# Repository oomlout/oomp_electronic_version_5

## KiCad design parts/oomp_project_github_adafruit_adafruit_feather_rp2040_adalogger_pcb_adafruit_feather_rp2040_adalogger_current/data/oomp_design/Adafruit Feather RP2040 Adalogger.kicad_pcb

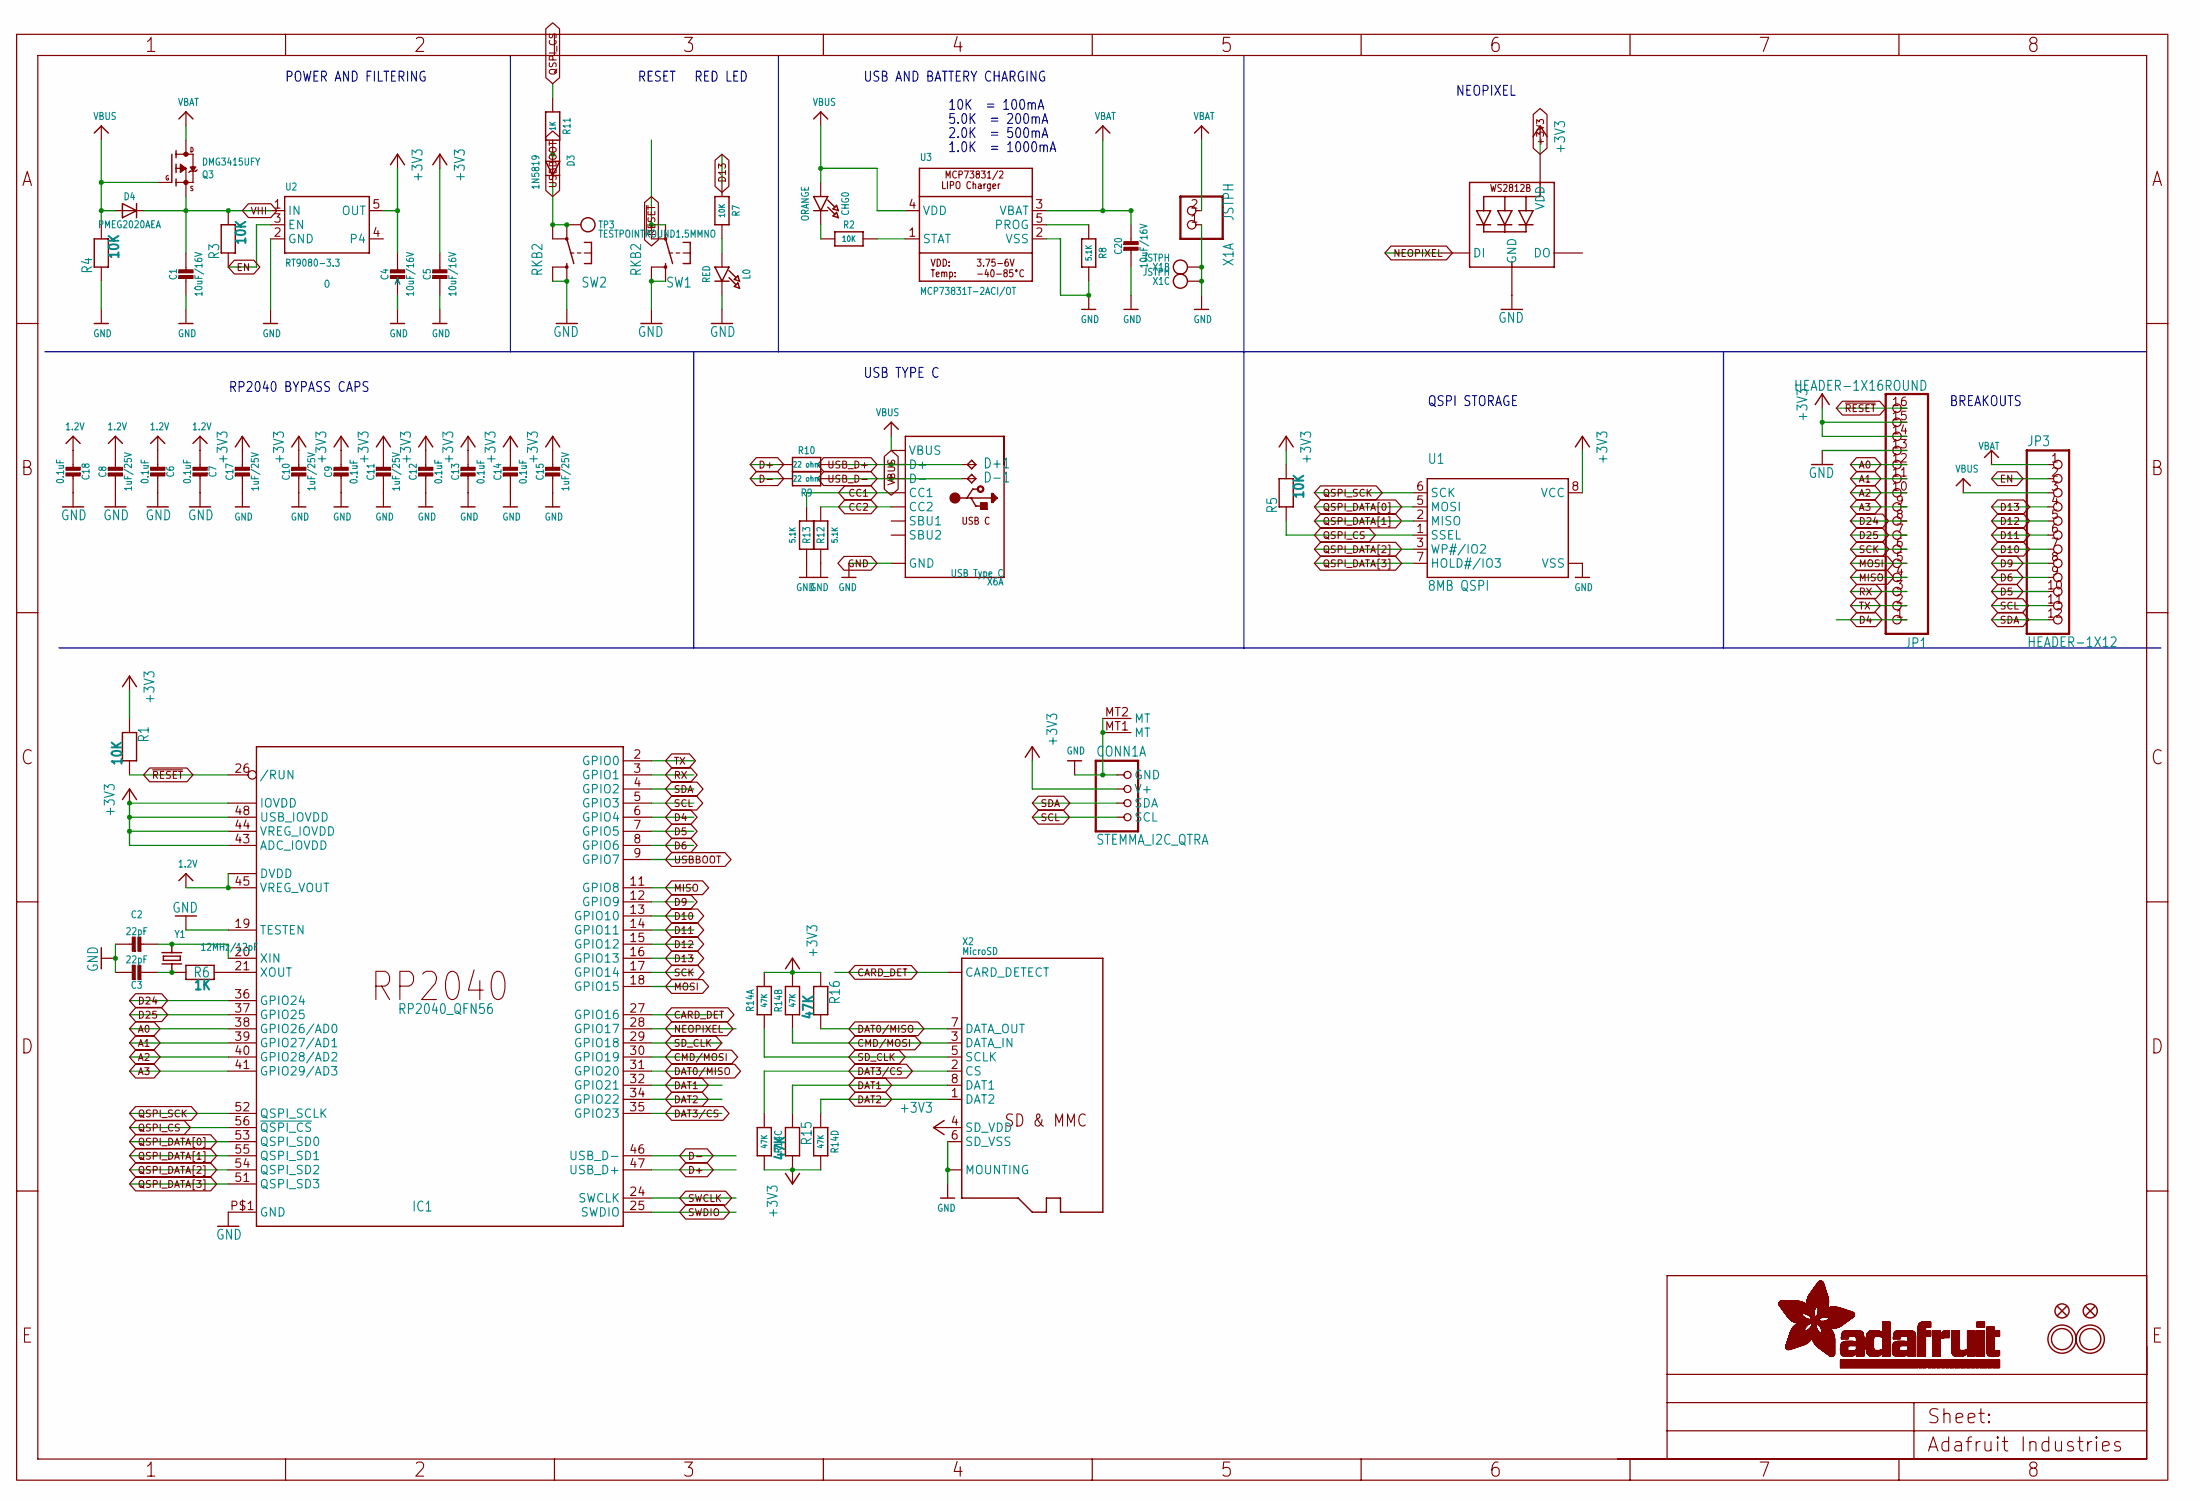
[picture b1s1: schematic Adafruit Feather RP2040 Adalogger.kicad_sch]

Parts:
C1, C4, C5, C20: 10uF/16V; 0805-NO
C2, C3: 22pF; _0402NO
C6, C7, C9, C12, C13, C14, C18: 0.1uF; _0402NO
C8, C10, C11, C15, C17: 1uF/25V; _0402NO
CHG0: ORANGE; CHIPLED_0603_NOOUTLINE
CONN1: STEMMA_I2C_QTRA; JST_SH4_RA; LCSC C145961
D3: 1N5819; SOD-323_MINI
D4: PMEG2020AEA; SOD-323F
D+1: TPB1,27; B1,27
D-1: TPB1,27; B1,27
IC1: RP2040_QFN56; QFN56_7MM_REDUCEDEPAD; LCSC C2040
JP1: HEADER-1X16ROUND; 1X16_ROUND
JP3: HEADER-1X12; 1X12_ROUND
L0: RED; CHIPLED_0603_NOOUTLINE
LED1: WS2812B_SK6805_1515; SK6805_1515; LCSC C2890035
Q3: DMG3415UFY; DFN2015-3
R1, R2, R3, R4, R5, R7: 10K; _0402NO
R6, R11: 1K; _0402NO
R8, R12, R13: 5.1K; _0402NO
R9, R10: 22 ohm; _0402NO
R14: 47K; RESPACK_4X0603
R15, R16: 47K; _0402NO
SW1, SW2: RKB2; BTN_RKB2_4.6X2.8
TP3: TESTPOINTROUND1.5MMNO; TESTPOINT_ROUND_1.5MM_NO
U1: 8MB QSPI; USON8_4X4
U2: RT9080-3.3; SOT23-5; JLC_ROTATION 0
U3: MCP73831T-2ACI/OT; SOT23-5; JLC_ROTATION 0
U$31, U$32: MOUNTINGHOLE2.5; MOUNTINGHOLE_2.5_PLATED
U$34, U$35: FIDUCIAL_1MM
X1: JSTPH; JSTPH2_BATT; LCSC C47647
X2: MicroSD; MICROSD; JLC_ROTATION 90
X6: USB Type C; USB_C_CUSB31-CFM2AX-01-X; LCSC C165948
Y1: 12MHz/12pF; CRYSTAL_2.5X2

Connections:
1.2V: C6.2, C7.2, C8.1, C18.2, IC1.23 (DVDD), IC1.45 (VREG_VOUT), IC1.50 (DVDD)
+3V3: C4.1, C5.1, C9.1, C10.1, C11.1, C12.1, C13.1, C14.1, C15.1, C17.1, CONN1.2 (V+), IC1.1 (IOVDD), IC1.10 (IOVDD), IC1.22 (IOVDD), IC1.33 (IOVDD), IC1.42 (IOVDD), IC1.43 (ADC_IOVDD), IC1.44 (VREG_IOVDD), IC1.48 (USB_IOVDD), IC1.49 (IOVDD), JP1.14, JP1.15, LED1.2 (VDD), R1.1, R5.2, R14.5 (2), R14.6 (2), R14.7 (2), R14.8 (2), R15.2, R16.1, U1.8 (VCC), U2.5 (OUT), X2.4 (SD_VDD)
A0: IC1.38 (GPIO26/AD0), JP1.12
A1: IC1.39 (GPIO27/AD1), JP1.11
A2: IC1.40 (GPIO28/AD2), JP1.10
A3: IC1.41 (GPIO29/AD3), JP1.9
CARD_DET: IC1.27 (GPIO16), X2.CD1 (CARD_DETECT), X2.CD2 (CARD_DETECT)
CC1: R13.2, X6.A5 (CC1)
CC2: R12.2, X6.B5 (CC2)
CMD/MOSI: IC1.30 (GPIO19), R14.2 (1), X2.3 (DATA_IN)
D4: IC1.6 (GPIO4), JP1.1
D5: IC1.7 (GPIO5), JP3.10
D6: IC1.8 (GPIO6), JP3.9
D9: IC1.12 (GPIO9), JP3.8
D10: IC1.13 (GPIO10), JP3.7
D11: IC1.14 (GPIO11), JP3.6
D12: IC1.15 (GPIO12), JP3.5
D13: IC1.16 (GPIO13), JP3.4, R7.1
D24: IC1.36 (GPIO24), JP1.8
D25: IC1.37 (GPIO25), JP1.7
D+: IC1.47 (USB_D+), R10.2
D-: IC1.46 (USB_D-), R9.2
DAT0/MISO: IC1.31 (GPIO20), R16.2, X2.7 (DATA_OUT)
DAT1: IC1.32 (GPIO21), R15.1, X2.8 (DAT1)
DAT2: IC1.34 (GPIO22), R14.4 (1), X2.1 (DAT2)
DAT3/CS: IC1.35 (GPIO23), R14.3 (1), X2.2 (CS)
EN: JP3.2, R3.1, U2.3 (EN)
GND: C1.2, C2.1, C3.1, C4.2, C5.2, C6.1, C7.1, C8.2, C9.2, C10.2, C11.2, C12.2, C13.2, C14.2, C15.2, C17.2, C18.1, C20.2, CONN1.1 (GND), CONN1.MT1 (MT), CONN1.MT2 (MT), IC1.19 (TESTEN), IC1.P$1 (GND), JP1.13, L0.C, LED1.4 (GND), R4.1, R8.2, R12.1, R13.1, SW1.B (S), SW1.B' (S1), SW2.B (S), SW2.B' (S1), U1.4 (VSS), U1.PAD (VSS), U2.2 (GND), U3.2 (VSS), X1.1, X1.NC1, X1.NC2, X2.6 (SD_VSS), X2.MT1 (MOUNTING), X2.MT2 (MOUNTING), X6.A1B12 (GND), X6.B1A12 (GND)
MISO: IC1.11 (GPIO8), JP1.4
MOSI: IC1.18 (GPIO15), JP1.5
unnamed: CHG0.C, R2.1
unnamed: L0.A, R7.2
unnamed: R2.2, U3.1 (STAT)
unnamed: R8.1, U3.5 (PROG)
unnamed: C2.2, IC1.20 (XIN), Y1.3 (2)
unnamed: C3.2, R6.1, Y1.1
unnamed: IC1.21 (XOUT), R6.2
unnamed: D3.A, R11.2
NEOPIXEL: IC1.28 (GPIO17), LED1.1 (DI)
QSPI_CS: IC1.56 (~QSPI_CS), R5.1, R11.1, U1.1 (SSEL)
QSPI_DATA[0]: IC1.53 (QSPI_SD0), U1.5 (MOSI)
QSPI_DATA[1]: IC1.55 (QSPI_SD1), U1.2 (MISO)
QSPI_DATA[2]: IC1.54 (QSPI_SD2), U1.3 (WP#/IO2)
QSPI_DATA[3]: IC1.51 (QSPI_SD3), U1.7 (HOLD#/IO3)
QSPI_SCK: IC1.52 (QSPI_SCLK), U1.6 (SCK)
RX: IC1.3 (GPIO1), JP1.3
SCK: IC1.17 (GPIO14), JP1.6
SCL: CONN1.4 (SCL), IC1.5 (GPIO3), JP3.11
SDA: CONN1.3 (SDA), IC1.4 (GPIO2), JP3.12
SD_CLK: IC1.29 (GPIO18), R14.1, X2.5 (SCLK)
SWCLK: IC1.24 (SWCLK)
SWDIO: IC1.25 (SWDIO)
TX: IC1.2 (GPIO0), JP1.2
USBBOOT: D3.C, IC1.9 (GPIO7), SW2.A, SW2.A' (P1), TP3.P$1
USB_D+: D+1.TP, R10.1, X6.A6 (D+), X6.B6 (D+)
USB_D-: D-1.TP, R9.1, X6.A7 (D-), X6.B7 (D-)
VBAT: C20.1, JP3.1, Q3.3 (D), U3.3 (VBAT), X1.2
VBUS: CHG0.A, D4.A, JP3.3, Q3.1 (G), R4.2, U3.4 (VDD), X6.A4B9 (VBUS), X6.B4A9 (VBUS)
VHI: C1.1, D4.C, Q3.2 (S), R3.2, U2.1 (IN)
~RESET: IC1.26 (/RUN), JP1.16, R1.2, SW1.A, SW1.A' (P1)

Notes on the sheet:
RP2040 BYPASS CAPS
POWER AND FILTERING
NEOPIXEL
QSPI STORAGE
USB AND BATTERY CHARGING
5.0K = 200mA
BREAKOUTS
RESET
10K = 100mA
RED LED
1.0K = 1000mA
2.0K = 500mA
USB TYPE C

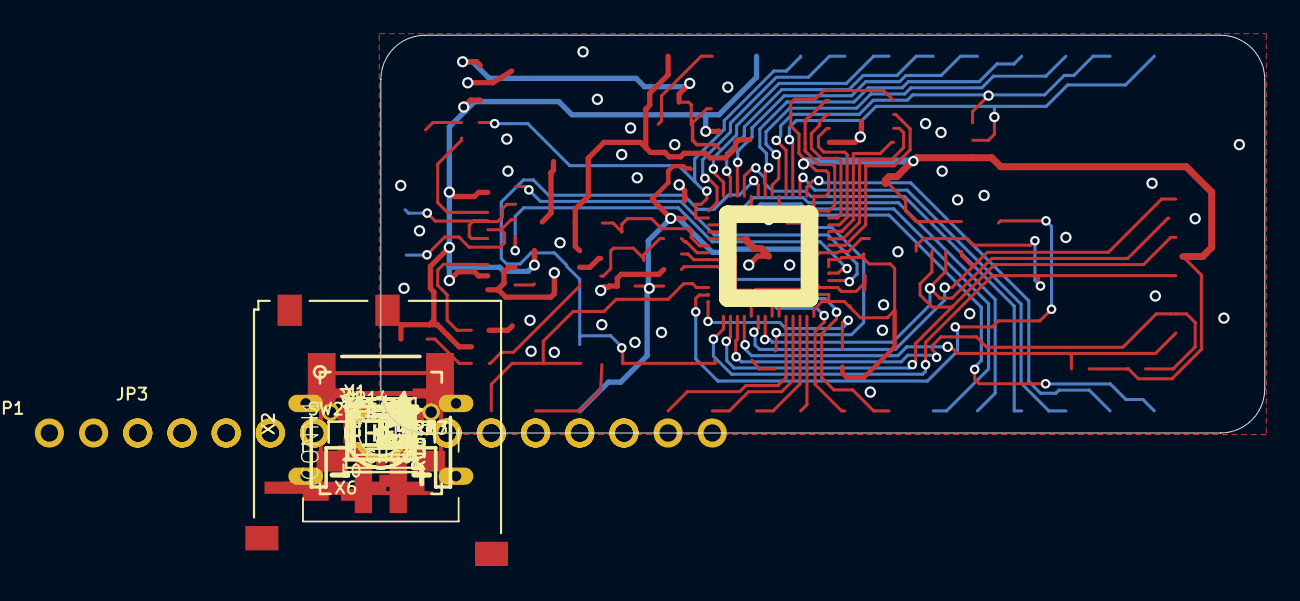
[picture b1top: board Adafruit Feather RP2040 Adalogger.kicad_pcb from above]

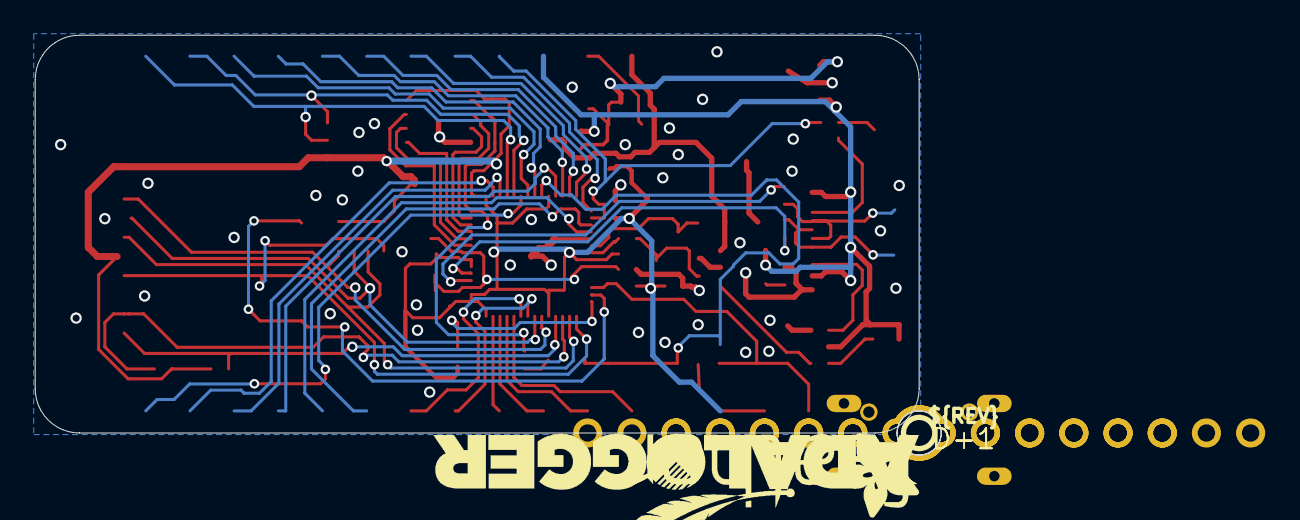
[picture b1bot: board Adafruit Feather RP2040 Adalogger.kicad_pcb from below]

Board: 2 copper layers, 50.8 x 22.9 mm, 130 parts (37 on the bottom side), 58 nets.

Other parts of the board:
PLABEL62: PLABEL62
PLABEL63: PLABEL63
PLABEL64: PLABEL64
PLABEL65: PLABEL65
PLABEL66: PLABEL66
PLABEL67: PLABEL67
PLABEL68: PLABEL68
PLABEL69: PLABEL69
PLABEL70: PLABEL70
PLABEL71: PLABEL71
PLABEL72: PLABEL72
PLABEL73: PLABEL73
PLABEL74: PLABEL74
PLABEL75: PLABEL75
PLABEL76: PLABEL76
PLABEL77: PLABEL77
PLABEL78: PLABEL78
PLABEL79: PLABEL79
PLABEL80: PLABEL80
PLABEL81: PLABEL81
PLABEL82: PLABEL82
PLABEL83: PLABEL83
PLABEL84: PLABEL84
PLABEL85: PLABEL85
PLABEL86: PLABEL86
PLABEL87: PLABEL87
PLABEL88: PLABEL88
PLABEL89: PLABEL89
PLABEL90: PLABEL90
PLABEL91: PLABEL91
PLABEL92: PLABEL92
PLABEL93: PLABEL93
PLABEL94: PLABEL94
PLABEL95: PLABEL95
PLABEL96: PLABEL96
PLABEL97: PLABEL97
PLABEL98: PLABEL98
PLABEL99: PLABEL99
PLABEL100: PLABEL100
PLABEL101: PLABEL101
PLABEL102: PLABEL102
PLABEL103: PLABEL103
PLABEL104: PLABEL104
PLABEL105: PLABEL105
PLABEL106: PLABEL106
PLABEL107: PLABEL107
PLABEL108: PLABEL108
PLABEL109: PLABEL109
PLABEL110: PLABEL110
PLABEL111: PLABEL111
PLABEL112: PLABEL112
PLABEL113: PLABEL113
PLABEL114: PLABEL114
PLABEL115: PLABEL115
PLABEL116: PLABEL116
PLABEL117: PLABEL117
PLABEL118: PLABEL118
PLABEL119: PLABEL119
PLABEL120: PLABEL120
PLABEL121: PLABEL121
PLABEL122: PLABEL122
PLABEL123: PLABEL123
PLABEL124: PLABEL124
U$13: PCBFEAT-REV-040
U$28: ADALOGGER_LOGO
U$43: ADAFRUIT_2.5MM
U$46: FEATHERLOGO_MED
U$47: ADAFRUIT_5MM
UNK_HOLE_0: dummyfp0
UNK_HOLE_1: dummyfp1

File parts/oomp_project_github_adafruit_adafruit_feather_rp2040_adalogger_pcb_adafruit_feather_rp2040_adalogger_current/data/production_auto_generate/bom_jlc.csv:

Comment,Designator,Footprint,LCSC Part #
,JP3,Adafruit Feather RP2040 Adalogger-import-fps:1X12_ROUND,C7501588
,JP1,Adafruit Feather RP2040 Adalogger-import-fps:1X16_ROUND,C7501270
,U$43,Adafruit Feather RP2040 Adalogger-import-fps:ADAFRUIT_2.5MM,
,U$47,Adafruit Feather RP2040 Adalogger-import-fps:ADAFRUIT_5MM,
,U$28,Adafruit Feather RP2040 Adalogger-import-fps:ADALOGGER_LOGO,
,U$46,Adafruit Feather RP2040 Adalogger-import-fps:FEATHERLOGO_MED,
,U$13,Adafruit Feather RP2040 Adalogger-import-fps:PCBFEAT-REV-040,
,PLABEL100,Adafruit Feather RP2040 Adalogger-import-fps:PLABEL100,
,PLABEL101,Adafruit Feather RP2040 Adalogger-import-fps:PLABEL101,
,PLABEL102,Adafruit Feather RP2040 Adalogger-import-fps:PLABEL102,
,PLABEL103,Adafruit Feather RP2040 Adalogger-import-fps:PLABEL103,
,PLABEL104,Adafruit Feather RP2040 Adalogger-import-fps:PLABEL104,
,PLABEL105,Adafruit Feather RP2040 Adalogger-import-fps:PLABEL105,
,PLABEL106,Adafruit Feather RP2040 Adalogger-import-fps:PLABEL106,
,PLABEL107,Adafruit Feather RP2040 Adalogger-import-fps:PLABEL107,
,PLABEL108,Adafruit Feather RP2040 Adalogger-import-fps:PLABEL108,
,PLABEL109,Adafruit Feather RP2040 Adalogger-import-fps:PLABEL109,
,PLABEL110,Adafruit Feather RP2040 Adalogger-import-fps:PLABEL110,
,PLABEL111,Adafruit Feather RP2040 Adalogger-import-fps:PLABEL111,
,PLABEL112,Adafruit Feather RP2040 Adalogger-import-fps:PLABEL112,
,PLABEL113,Adafruit Feather RP2040 Adalogger-import-fps:PLABEL113,
,PLABEL114,Adafruit Feather RP2040 Adalogger-import-fps:PLABEL114,
,PLABEL115,Adafruit Feather RP2040 Adalogger-import-fps:PLABEL115,
,PLABEL116,Adafruit Feather RP2040 Adalogger-import-fps:PLABEL116,
,PLABEL117,Adafruit Feather RP2040 Adalogger-import-fps:PLABEL117,
,PLABEL118,Adafruit Feather RP2040 Adalogger-import-fps:PLABEL118,
,PLABEL119,Adafruit Feather RP2040 Adalogger-import-fps:PLABEL119,
,PLABEL120,Adafruit Feather RP2040 Adalogger-import-fps:PLABEL120,
,PLABEL121,Adafruit Feather RP2040 Adalogger-import-fps:PLABEL121,
,PLABEL122,Adafruit Feather RP2040 Adalogger-import-fps:PLABEL122,
,PLABEL123,Adafruit Feather RP2040 Adalogger-import-fps:PLABEL123,
,PLABEL124,Adafruit Feather RP2040 Adalogger-import-fps:PLABEL124,
,PLABEL62,Adafruit Feather RP2040 Adalogger-import-fps:PLABEL62,
,PLABEL63,Adafruit Feather RP2040 Adalogger-import-fps:PLABEL63,
,PLABEL64,Adafruit Feather RP2040 Adalogger-import-fps:PLABEL64,
,PLABEL65,Adafruit Feather RP2040 Adalogger-import-fps:PLABEL65,
,PLABEL66,Adafruit Feather RP2040 Adalogger-import-fps:PLABEL66,
,PLABEL67,Adafruit Feather RP2040 Adalogger-import-fps:PLABEL67,
,PLABEL68,Adafruit Feather RP2040 Adalogger-import-fps:PLABEL68,
,PLABEL69,Adafruit Feather RP2040 Adalogger-import-fps:PLABEL69,
,PLABEL70,Adafruit Feather RP2040 Adalogger-import-fps:PLABEL70,
,PLABEL71,Adafruit Feather RP2040 Adalogger-import-fps:PLABEL71,
,PLABEL72,Adafruit Feather RP2040 Adalogger-import-fps:PLABEL72,
,PLABEL73,Adafruit Feather RP2040 Adalogger-import-fps:PLABEL73,
,PLABEL74,Adafruit Feather RP2040 Adalogger-import-fps:PLABEL74,
,PLABEL75,Adafruit Feather RP2040 Adalogger-import-fps:PLABEL75,
,PLABEL76,Adafruit Feather RP2040 Adalogger-import-fps:PLABEL76,
,PLABEL77,Adafruit Feather RP2040 Adalogger-import-fps:PLABEL77,
,PLABEL78,Adafruit Feather RP2040 Adalogger-import-fps:PLABEL78,
,PLABEL79,Adafruit Feather RP2040 Adalogger-import-fps:PLABEL79,
,PLABEL80,Adafruit Feather RP2040 Adalogger-import-fps:PLABEL80,
,PLABEL81,Adafruit Feather RP2040 Adalogger-import-fps:PLABEL81,
,PLABEL82,Adafruit Feather RP2040 Adalogger-import-fps:PLABEL82,
,PLABEL83,Adafruit Feather RP2040 Adalogger-import-fps:PLABEL83,
,PLABEL84,Adafruit Feather RP2040 Adalogger-import-fps:PLABEL84,
,PLABEL85,Adafruit Feather RP2040 Adalogger-import-fps:PLABEL85,
,PLABEL86,Adafruit Feather RP2040 Adalogger-import-fps:PLABEL86,
,PLABEL87,Adafruit Feather RP2040 Adalogger-import-fps:PLABEL87,
,PLABEL88,Adafruit Feather RP2040 Adalogger-import-fps:PLABEL88,
,PLABEL89,Adafruit Feather RP2040 Adalogger-import-fps:PLABEL89,
,PLABEL90,Adafruit Feather RP2040 Adalogger-import-fps:PLABEL90,
,PLABEL91,Adafruit Feather RP2040 Adalogger-import-fps:PLABEL91,
,PLABEL92,Adafruit Feather RP2040 Adalogger-import-fps:PLABEL92,
,PLABEL93,Adafruit Feather RP2040 Adalogger-import-fps:PLABEL93,
,PLABEL94,Adafruit Feather RP2040 Adalogger-import-fps:PLABEL94,
,PLABEL95,Adafruit Feather RP2040 Adalogger-import-fps:PLABEL95,
,PLABEL96,Adafruit Feather RP2040 Adalogger-import-fps:PLABEL96,
,PLABEL97,Adafruit Feather RP2040 Adalogger-import-fps:PLABEL97,
,PLABEL98,Adafruit Feather RP2040 Adalogger-import-fps:PLABEL98,
,PLABEL99,Adafruit Feather RP2040 Adalogger-import-fps:PLABEL99,
,TP3,Adafruit Feather RP2040 Adalogger-import-fps:TESTPOINT_ROUND_1.5MM_NO,
0.1uF,"C6,C7,C9,C12,C13,C14,C18",Adafruit Feather RP2040 Adalogger-import-fps:_0402NO,C60474
10K,"R1,R2,R3,R4,R5,R7",Adafruit Feather RP2040 Adalogger-import-fps:_0402NO,C2906861
10uF/16V,"C1,C4,C5,C20",Adafruit Feather RP2040 Adalogger-import-fps:0805-NO,
12MHz/12pF,Y1,Adafruit Feather RP2040 Adalogger-import-fps:CRYSTAL_2.5X2,
1K,"R6,R11",Adafruit Feather RP2040 Adalogger-import-fps:_0402NO,C2906864
1N5819,D3,Adafruit Feather RP2040 Adalogger-import-fps:SOD-323_MINI,
1uF/25V,"C8,C10,C11,C15,C17",Adafruit Feather RP2040 Adalogger-import-fps:_0402NO,C2887021
22 ohm,"R9,R10",Adafruit Feather RP2040 Adalogger-import-fps:_0402NO,C114765
22pF,"C2,C3",Adafruit Feather RP2040 Adalogger-import-fps:_0402NO,C106203
47K,"R15,R16",Adafruit Feather RP2040 Adalogger-import-fps:_0402NO,C25792
47K,R14,Adafruit Feather RP2040 Adalogger-import-fps:RESPACK_4X0603,C2907042
5.1K,"R8,R12,R13",Adafruit Feather RP2040 Adalogger-import-fps:_0402NO,C25905
8MB QSPI,U1,Adafruit Feather RP2040 Adalogger-import-fps:USON8_4X4,
DMG3415UFY,Q3,Adafruit Feather RP2040 Adalogger-import-fps:DFN2015-3,
FIDUCIAL_1MM,"U$34,U$35",Adafruit Feather RP2040 Adalogger-import-fps:FIDUCIAL_1MM,
JSTPH,X1,Adafruit Feather RP2040 Adalogger-import-fps:JSTPH2_BATT,
MCP73831T-2ACI/OT,U3,Adafruit Feather RP2040 Adalogger-import-fps:SOT23-5,
MicroSD,X2,Adafruit Feather RP2040 Adalogger-import-fps:MICROSD,
ORANGE,CHG0,Adafruit Feather RP2040 Adalogger-import-fps:CHIPLED_0603_NOOUTLINE,
PMEG2020AEA,D4,Adafruit Feather RP2040 Adalogger-import-fps:SOD-323F,
RED,L0,Adafruit Feather RP2040 Adalogger-import-fps:CHIPLED_0603_NOOUTLINE,
RKB2,"SW1,SW2",Adafruit Feather RP2040 Adalogger-import-fps:BTN_RKB2_4.6X2.8,
RP2040_QFN56,IC1,Adafruit Feather RP2040 Adalogger-import-fps:QFN56_7MM_REDUCEDEPAD,
RT9080-3.3,U2,Adafruit Feather RP2040 Adalogger-import-fps:SOT23-5,
STEMMA_I2C_QTRA,CONN1,Adafruit Feather RP2040 Adalogger-import-fps:JST_SH4_RA,
"TPB1,27","D+1,D-1","Adafruit Feather RP2040 Adalogger-import-fps:B1,27",
USB Type C,X6,Adafruit Feather RP2040 Adalogger-import-fps:USB_C_CUSB31-CFM2AX-01-X,
WS2812B_SK6805_1515,LED1,Adafruit Feather RP2040 Adalogger-import-fps:SK6805_1515,
